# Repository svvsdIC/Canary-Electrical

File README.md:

# Canary-Electrical
Board files and schematics for Canary project

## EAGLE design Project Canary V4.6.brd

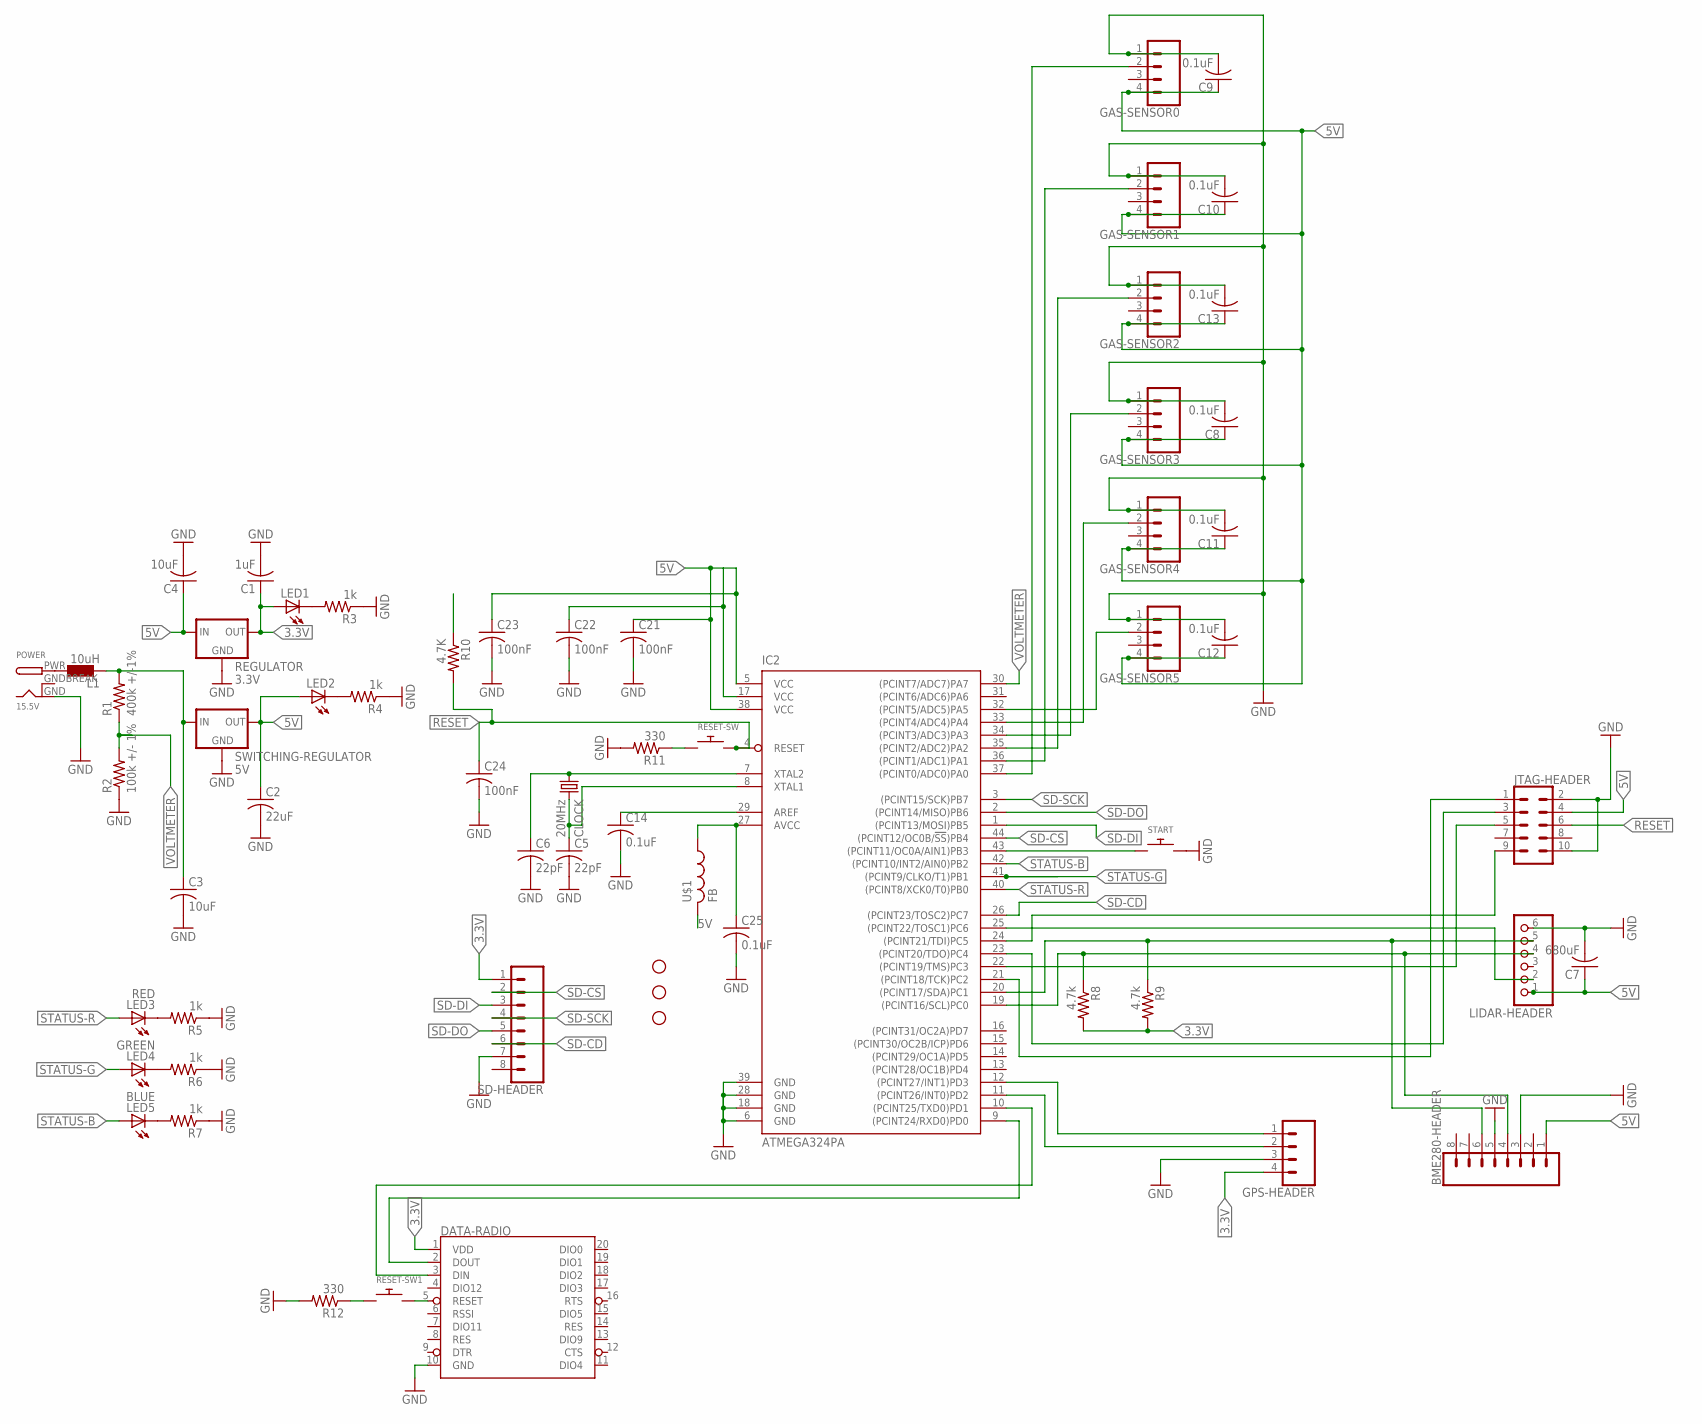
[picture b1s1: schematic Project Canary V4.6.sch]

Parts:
BME280-HEADER: CONN_08"; 1X08
C1: 1uF; C0805
C2: 22uF; C0603
C3: 10uF; C0805
C4: 10uF; C0603
C5, C6: 22pF; C0603
C7: 680uF; C0603
C8, C9, C10, C11, C12, C13, C14, C25: 0.1uF; C0603
C21, C22, C23: 100nF; C0603
C24: 100nF; C0805
CLOCK: 20MHz; 86SMX
DATA-RADIO: XBEE
GAS-SENSOR0, GAS-SENSOR1, GAS-SENSOR2, GAS-SENSOR3, GAS-SENSOR4, GAS-SENSOR5: CONN_04; 1X04
GPS-HEADER: CONN_04; 1X04
IC2: ATMEGA324PA; TQFP44
JTAG-HEADER: CONN_05X2PTH; 2X5
L1: 10uH; L1812
LED1, LED2: LEDCHIP-LED0805; CHIP-LED0805
LED3: RED; CHIP-LED0805
LED4: GREEN; CHIP-LED0805
LED5: BLUE; CHIP-LED0805
LIDAR-HEADER: PINHD-1X6; 1X06
MOUNT-HOLE1, MOUNT-HOLE2, MOUNT-HOLE3: STAND-OFF
POWER: 15.5V; DCJACK_2MM_PTH
R1: 400k +/-1%; M0805
R2: 100k +/- 1%; M0805
R3, R4, R5, R6, R7: 1k; M0805
R8, R9: 4.7k; M0805
R10: 4.7K; M0805
R11, R12: 330; M0805
REGULATOR: 3.3V; TO220-IGO
RESET-SW, RESET-SW1: SWITCH_PUSHBUTTONSOFTTOUCHSMD_SJ; PUSHBUTTON_SMD_SJ
SD-HEADER: CONN_08"; 1X08
START: SWITCH_PUSHBUTTONSOFTTOUCHSMD_SJ; PUSHBUTTON_SMD_SJ
SWITCHING-REGULATOR: 5V; TO220-IGO
U$1: FB

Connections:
3.3V: C1.1, DATA-RADIO.1 (VDD), GPS-HEADER.4, LED1.A, R8.2, R9.2, REGULATOR.OUT, SD-HEADER.1
5V: BME280-HEADER.1, C2.1, C4.1, C7.1, C8.1, C9.1, C10.1, C11.1, C12.1, C13.1, C21.1, C22.1, C23.1, GAS-SENSOR0.4, GAS-SENSOR1.4, GAS-SENSOR2.4, GAS-SENSOR3.4, GAS-SENSOR4.4, GAS-SENSOR5.4, IC2.5 (VCC), IC2.17 (VCC), IC2.38 (VCC), JTAG-HEADER.4, LED2.A, LIDAR-HEADER.1, REGULATOR.IN, SWITCHING-REGULATOR.OUT, U$1.P$2 (2)
GND: BME280-HEADER.3, BME280-HEADER.5, C1.2, C2.2, C3.2, C4.2, C5.2, C6.2, C7.2, C8.2, C9.2, C10.2, C11.2, C12.2, C13.2, C14.2, C21.2, C22.2, C23.2, C24.2, C25.2, DATA-RADIO.10 (GND), GAS-SENSOR0.1, GAS-SENSOR1.1, GAS-SENSOR2.1, GAS-SENSOR3.1, GAS-SENSOR4.1, GAS-SENSOR5.1, GPS-HEADER.3, IC2.6 (GND), IC2.18 (GND), IC2.28 (GND), IC2.39 (GND), JTAG-HEADER.2, JTAG-HEADER.10, LIDAR-HEADER.6, POWER.GND, R2.1, R3.1, R4.1, R5.1, R6.1, R7.1, R11.2, R12.2, REGULATOR.GND, SD-HEADER.7, START.P$2, SWITCHING-REGULATOR.GND
GNDBREAK: POWER.GNDBREAK
unnamed: C3.1, L1.2, R1.2, SWITCHING-REGULATOR.IN
unnamed: LED1.C, R3.2
unnamed: LED2.C, R4.2
unnamed: LED3.C, R5.2
unnamed: LED4.C, R6.2
unnamed: LED5.C, R7.2
unnamed: IC2.43 ((PCINT11/OC0A/AIN1)PB3), START.P$1
unnamed: C6.1, CLOCK.1, IC2.7 (XTAL2)
unnamed: C25.1, IC2.27 (AVCC), U$1.P$1 (1)
unnamed: GPS-HEADER.1, IC2.12 ((PCINT27/INT1)PD3)
unnamed: GPS-HEADER.2, IC2.11 ((PCINT26/INT0)PD2)
unnamed: GAS-SENSOR0.2, IC2.37 ((PCINT0/ADC0)PA0)
unnamed: IC2.25 ((PCINT22/TOSC1)PC6), LIDAR-HEADER.2
unnamed: IC2.24 ((PCINT21/TDI)PC5), JTAG-HEADER.9
unnamed: C14.1, IC2.29 (AREF)
unnamed: GAS-SENSOR1.2, IC2.36 ((PCINT1/ADC1)PA1)
unnamed: GAS-SENSOR2.2, IC2.35 ((PCINT2/ADC2)PA2)
unnamed: GAS-SENSOR3.2, IC2.34 ((PCINT3/ADC3)PA3)
unnamed: GAS-SENSOR4.2, IC2.33 ((PCINT4/ADC4)PA4)
unnamed: GAS-SENSOR5.2, IC2.32 ((PCINT5/ADC5)PA5)
unnamed: BME280-HEADER.4, IC2.19 ((PCINT16/SCL)PC0), LIDAR-HEADER.4, R8.1
unnamed: L1.1, POWER.PWR
unnamed: IC2.23 ((PCINT20/TDO)PC4), JTAG-HEADER.3
unnamed: BME280-HEADER.6, IC2.20 ((PCINT17/SDA)PC1), LIDAR-HEADER.5, R9.1
unnamed: IC2.22 ((PCINT19/TMS)PC3), JTAG-HEADER.5
unnamed: DATA-RADIO.3 (DIN), IC2.10 ((PCINT25/TXD0)PD1)
unnamed: DATA-RADIO.2 (DOUT), IC2.9 ((PCINT24/RXD0)PD0)
unnamed: IC2.21 ((PCINT18/TCK)PC2), JTAG-HEADER.1
unnamed: DATA-RADIO.5 (RESET), RESET-SW1.P$2
unnamed: R11.1, RESET-SW.P$1
unnamed: C5.1, CLOCK.4 (2), IC2.8 (XTAL1)
unnamed: R12.1, RESET-SW1.P$1
RESET: C24.1, IC2.4 (RESET), JTAG-HEADER.6, R10.2, RESET-SW.P$2
SD-CD: IC2.26 ((PCINT23/TOSC2)PC7), SD-HEADER.6
SD-CS: IC2.44 ((PCINT12/OC0B/!SS!)PB4), SD-HEADER.2
SD-DI: IC2.1 ((PCINT13/MOSI)PB5), SD-HEADER.3
SD-DO: IC2.2 ((PCINT14/MISO)PB6), SD-HEADER.5
SD-SCK: IC2.3 ((PCINT15/SCK)PB7), SD-HEADER.4
STATUS-B: IC2.42 ((PCINT10/INT2/AIN0)PB2), LED5.A
STATUS-G: IC2.41 ((PCINT9/CLKO/T1)PB1), LED4.A
STATUS-R: IC2.40 ((PCINT8/XCK0/T0)PB0), LED3.A
VOLTMETER: IC2.30 ((PCINT7/ADC7)PA7), R1.1, R2.2

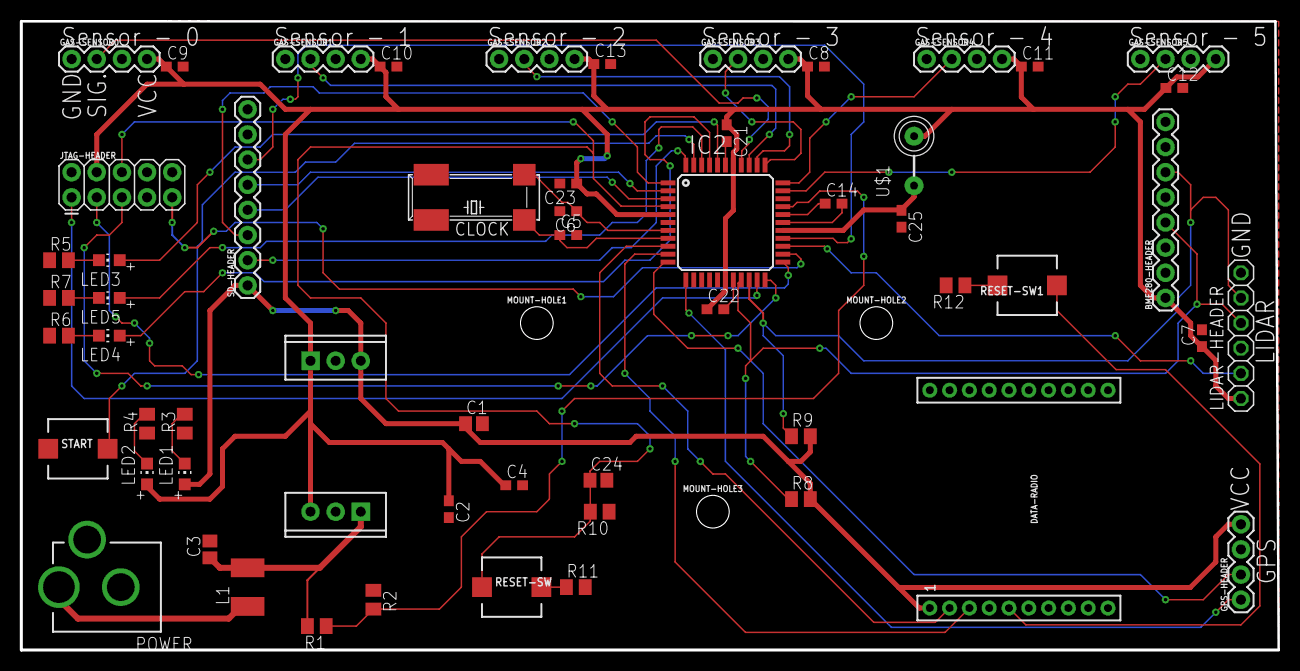
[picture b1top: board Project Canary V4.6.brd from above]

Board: 2 copper layers, 127.0 x 63.5 mm, 61 parts (0 on the bottom side), 45 nets.

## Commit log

2018-03-16 Initial commit of Canary board and schematic
    Added:
    -CanarySchematic3.0.brd
    - CanarySchematic3.0.sch
2018-04-13 Finished circuit board layout
    Finished routing all the airwires
    Need to adjust the widths of the 5V and 3.3V airwires to allow for 1.5A and .25A, respectively
2018-04-20 Increasing the width of the power lines
    Per Pete's advice, I increased the width of all the routes for the 3.3V and 5V lines
    Increased the isolate the top and bottom ground pours to 12 mils
    Made some minor adjustments to some of the routes
2018-06-01 Fixed some of the DRC Errors
    * Found the two remaining airwires and routed them
    * Fixed the clearance errors on some of the resistors
    * Ended up with 482 errors for the widths of the routes
2018-06-08 Finalizing the details of the board
    * Isolated the groundpour of the board from 10 mils to 12 mils
    * Rerouted all the lines to get rid of the DRC width errors
2018-10-16 Final draft of Project Canary circuit board
    - Widened the power lines near the plug to 24 mils, and some routes branching off to 8 mils
    - Added labels for each of the sensors (sensor #, GND, signal, VCC), and the LIDAR and GPS headers
2018-10-16 Final final draft of circuit board
    - Modified the reset for the data radio to match the one on the micro controller (added a reset button and 330 Ohm resistor before connecting to GND) in the schematic
    - Added routes to the reset button and resistor (R12) after placing them above the data radio on the board; the route from the radio to the reset button wraps around the GPS header
2019-06-13 Added ground to pin 5, (bottom right)
2019-06-13 Organized file
2019-06-13 Fixed the Ferrite Bead and smoothed out wires

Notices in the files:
parts and their libraries:
SparkFun-Connectors: Licensing: Creative Commons ShareAlike 4.0 International - https://creativecommons.org/licenses/by-sa/4.0
